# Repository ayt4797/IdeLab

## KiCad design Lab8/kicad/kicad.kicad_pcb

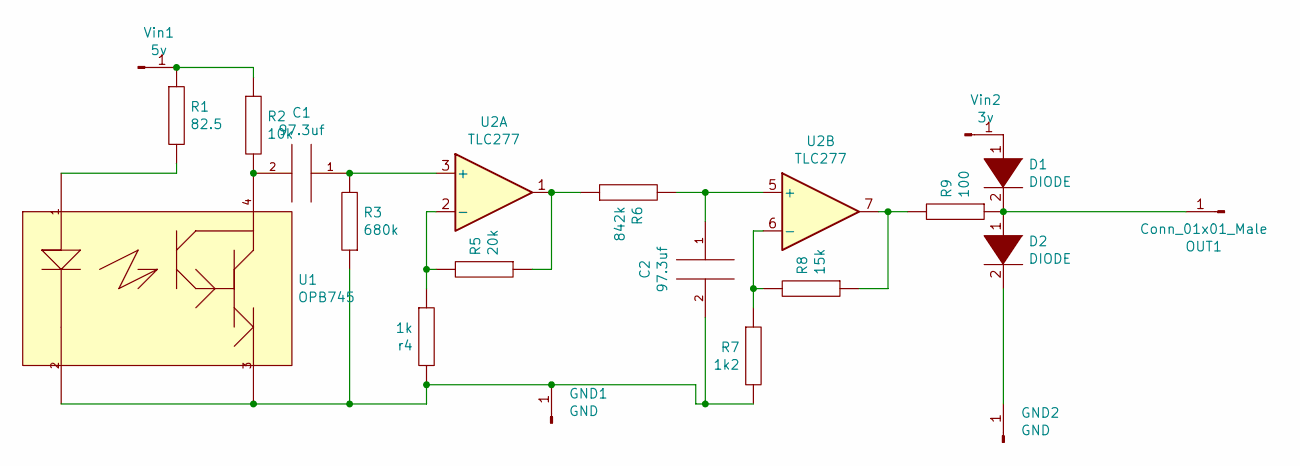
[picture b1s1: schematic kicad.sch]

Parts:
1k2: R7; R_Axial_DIN0204_L3.6mm_D1.6mm_P1.90mm_Vertical
C1, C2: 97.3uf; CP_Radial_D4.0mm_P1.50mm
D1, D2: DIODE; CP_Axial_L10.0mm_D4.5mm_P15.00mm_Horizontal
GND1, GND2: GND; PinHeader_1x01_P2.54mm_Horizontal
OUT1: Conn_01x01_Male; PinHeader_1x01_P2.54mm_Horizontal
R1: 82.5; R_Axial_DIN0204_L3.6mm_D1.6mm_P1.90mm_Vertical
R2: 10k; R_Axial_DIN0204_L3.6mm_D1.6mm_P1.90mm_Vertical
R3: 680k; R_Axial_DIN0204_L3.6mm_D1.6mm_P1.90mm_Vertical
R5: 20k; R_Axial_DIN0204_L3.6mm_D1.6mm_P1.90mm_Vertical
R6: 842k; R_Axial_DIN0204_L3.6mm_D1.6mm_P1.90mm_Vertical
R8: 15k; R_Axial_DIN0204_L3.6mm_D1.6mm_P1.90mm_Vertical
R9: 100; R_Axial_DIN0204_L3.6mm_D1.6mm_P1.90mm_Vertical
U1: OPB745; PinHeader_1x04_P2.54mm_Vertical; voltage 15V; mouser part number 828-OPB745; digikey description SENSR OPTO TRANS 3.81MM REFL PCB
U2: TLC277; DIP794W45P254L959H508Q8
Vin1: 5v; PinHeader_1x01_P2.54mm_Horizontal
Vin2: 3v; PinHeader_1x01_P2.54mm_Horizontal
r4: 1k; R_Axial_DIN0204_L3.6mm_D1.6mm_P1.90mm_Vertical

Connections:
unnamed: 1k2.1, R8.2, U2.6 (-)
unnamed: 1k2.2, C2.2, GND1.1, R3.1, U1.2 (Cathode), U1.3 (Emitter), r4.2
unnamed: C1.1, R3.2, U2.3 (+)
unnamed: C1.2, R2.2, U1.4 (Collector)
unnamed: C2.1, R6.2, U2.5 (+)
unnamed: D1.1 (K), Vin2.1
unnamed: D1.2 (A), D2.1 (K), OUT1.1, R9.1
unnamed: D2.2 (A), GND2.1
unnamed: R1.1, R2.1, Vin1.1
unnamed: R1.2, U1.1 (Anode)
unnamed: R5.1, R6.1, U2.1
unnamed: R5.2, U2.2 (-), r4.1
unnamed: R8.1, R9.2, U2.7

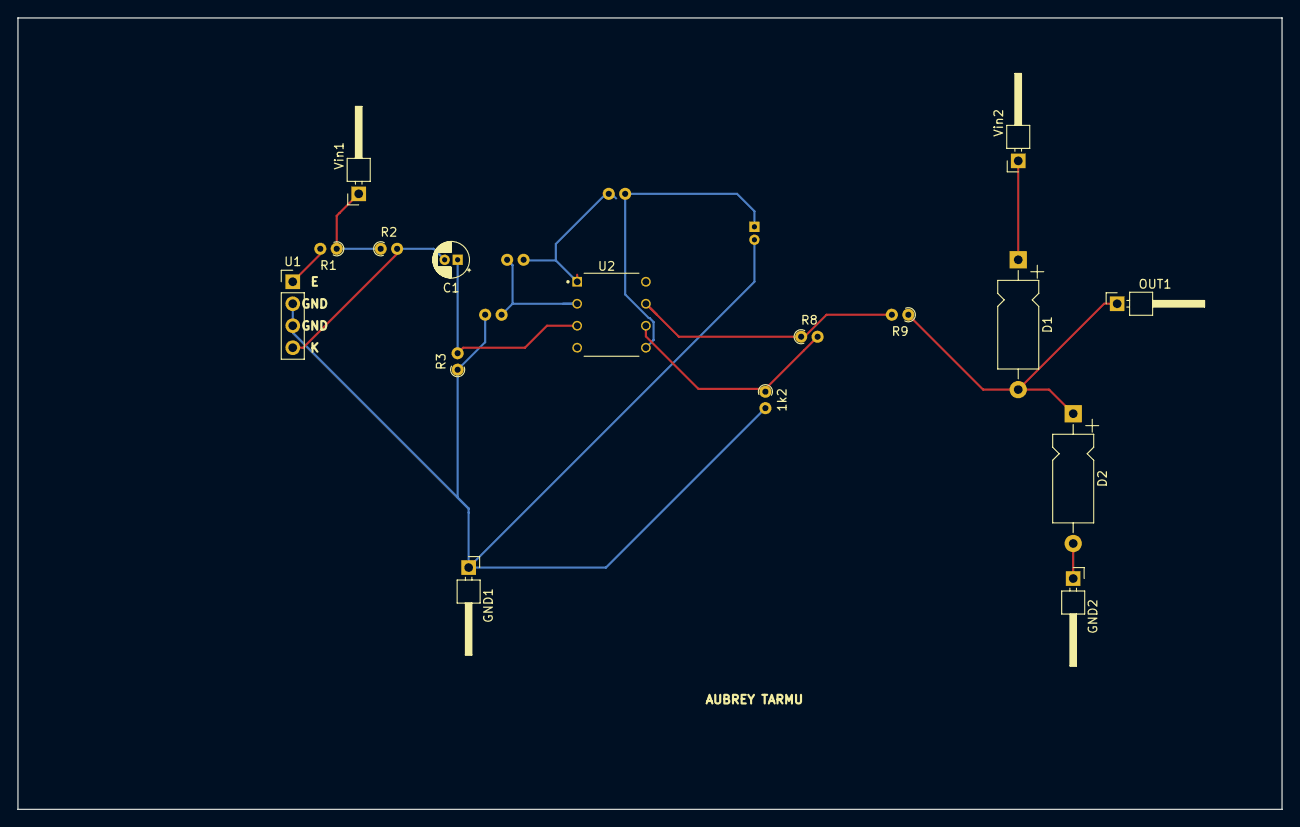
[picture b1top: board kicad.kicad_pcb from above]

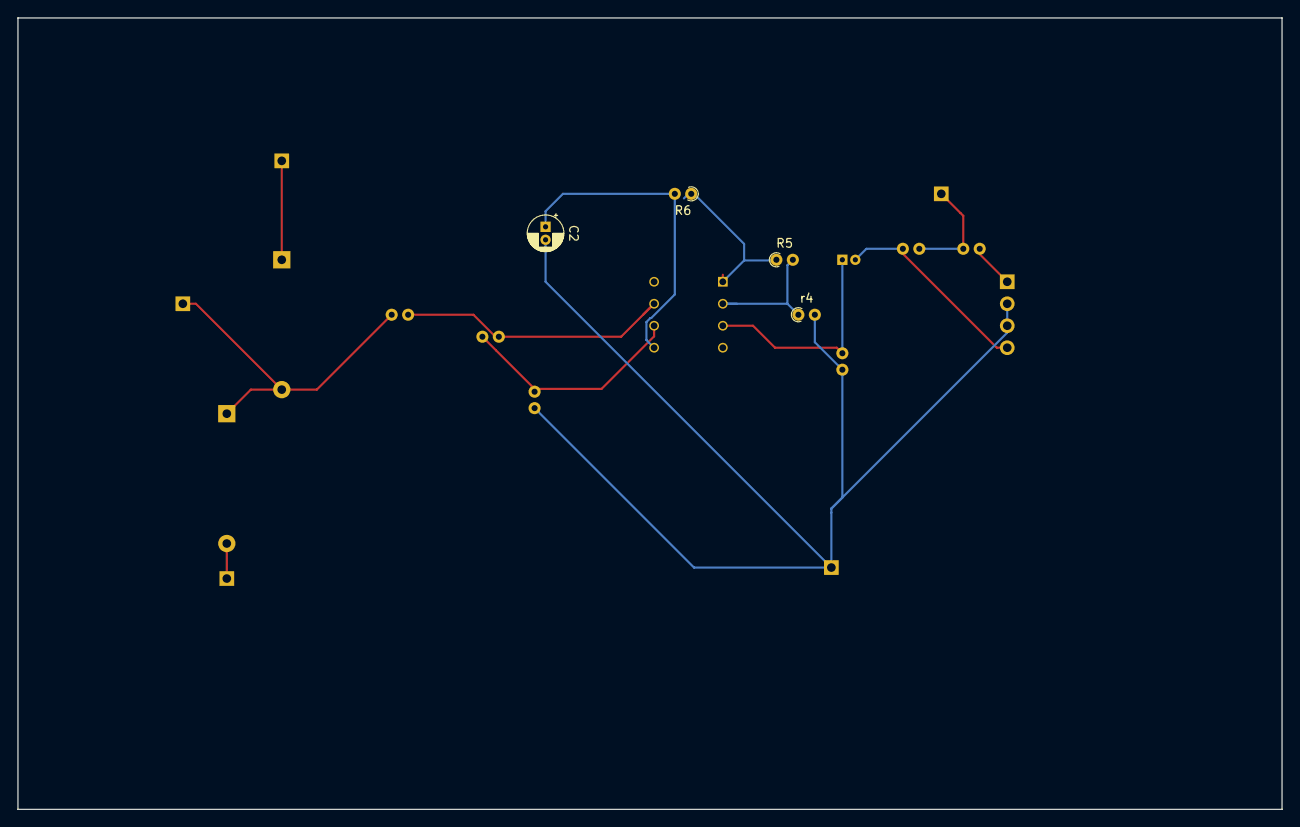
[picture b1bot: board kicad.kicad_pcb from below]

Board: 32 copper layers, 146.0 x 91.4 mm, 20 parts (4 on the bottom side), 13 nets.

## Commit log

2021-09-22 start
2021-09-24 work from friday lab
2021-10-01 part2a
2021-10-01 finished part2b
2021-10-01 systickTimer
2021-10-01 part3 start
2021-10-05 Dante's stuff
2021-10-08 real start
2021-10-09 lab 5 final
2021-10-14 10-14-21 working motor, but weird
2021-10-15 fcking git
2021-10-15 checkoff
2021-10-16 started part 3
2021-10-19 servo spinned
2021-10-19 minor changes
2021-10-21 check off part 3
2021-10-21 dante changes
2021-10-22 lab7 start
2021-10-22 100nf
2021-10-22 first order
2021-10-22 three order
2021-10-22 check off
2021-10-22 Added Lab6Stepper
2021-10-22 Added DCMotor
2021-10-22 Update DCMotor
2021-10-28 tst2
2021-10-28 reset file
2021-10-28 finnish sallen key
2021-10-28 butterworth
2021-10-28 fcking github
2021-10-29 finished
2021-10-29 prelab
2021-10-29 started adc
2021-10-29 labreport start lab7
2021-10-29 fixed the sallen key:
2021-11-04 fixing some small things w/ lab8 file
2021-11-04 basically haven't moved
2021-11-05 sign off 8
2021-11-06 project1 start
2021-11-06 added in lab4 stuff
2021-11-06 testing oled
2021-11-06 rewriting to print to both putty & bluetooth
2021-11-06 11/06/2021 Milestone 1 Almost Done
2021-11-06 bluetooth and oled setup
2021-11-06 moved the oled stuff to top
2021-11-06 balls
2021-11-06 added some stuff to my lab8
2021-11-06 nearly done w/8
2021-11-06 Near-final Milestone 1. Sign off required. Kp may need to be adjusted
2021-11-07 lab08
2021-11-07 nearly done w/ lab08
2021-11-08 removed that debug statement
2021-11-08 testing
2021-11-08 some kicad stuff
2021-11-08 near checkoff
2021-11-08 added osh screenshots
2021-11-08 added macros
2021-11-08 added some more directional control
2021-11-08 added some comments and a tolerance in case there's a camera mistake in the middle
2021-11-10 Corrections to inital commit
2021-11-10 Assembly changes
2021-11-10 Basic changes. Added debugging tools. Flipped Camera around. Found an issue with i being double defined from a for loop in the turn_left() function. Also renamed some functions
2021-11-10 Fucked with Integration time and camera focus. Camera scene is now 11791179
2021-11-11 Non ideal steering fix. based on main branch. Tolerance code is needed to minimize steering until absolutley need
2021-11-11 Additional changes to Kp. Changes to definition of control may be required
2021-11-11 theory
2021-11-11 Veriifed camera works
2021-11-11 Added debug changes. Changed integration time to match playingAround branch
2021-11-11 Adjusted integration time, adjusted thresehold. Overall pulled camera configuartion from playingAround
2021-11-11 New steering code
2021-11-11 Added fetch of current left and right to new steering
2021-11-11 Milestone 1 - recomplished
2021-11-11 derp
2021-11-11 Milestone 2 complete!
2021-11-11 Minor tweaks to speed and gain of proportional control
2021-11-11 removed old steering code
2021-11-12 found where the issue is, will ask seth for advice
2021-11-12 bluetooth works
2021-11-12 fixed some things
2021-11-12 fixed the clearance issue
2021-11-12 Refactoring of PID. Split up servo adjust for readability. Commeneted out BL adjustment since it needs to be cleaned up
2021-11-12 Minor changes.
2021-11-13 pcb done
2021-11-14 fixed some stuff
2021-11-15 Inital electric differential control
2021-11-15 Resolved error
2021-11-15 Minimum viable product. Includes straight away full bore speed. And moderatly refined P control
2021-11-15 working pid
2021-11-15 milestone 3
2021-11-15 Minor refactoring of PID solution
2021-11-17 Added new method to track going straight. Increased BAUD RATE to 115200. Added optimization logic
2021-11-18 Implemented PID. Minor oscillation still. Effective MVP
2021-11-18 MVP - Minor oscillations with PID on curvy track. She'll work tho. 70% of the time?
2021-11-18 MVP - Could use tolerance on going straight but otherwise PID control is 936$
2021-11-20 Changes made. Turning needs to be a lot more precise
2021-11-29 Reserve Commit
2021-12-01 Lowest Possible Speed
2021-12-01 added a left&right PID
2021-12-01 Preserving Recent Changes from today
2021-12-01 Debugging bad issues with turning right.
2021-12-01 fixed it poorly
2021-12-02 MVP 12/1/2021
2021-12-02 PID changes, turning speed changes required. New Braking system. Integration Hell. Will work with slower speeds
2021-12-02 cleaned some global variables
2021-12-03 mor minor things
2021-12-03 stuff
2021-12-03 more cleaning
2021-12-03 last clean
2021-12-03 kinda working
2021-12-03 super safe mode
2021-12-03 45sec
2021-12-03 removed old speed up stuff and fixed speed up
2021-12-03 increased gain
2021-12-03 some cleaning
2021-12-04 Inital commit from MVP_12_2_2021
2021-12-04 beginning of super safe mode
2021-12-04 went around the main track
2021-12-04 doesn't work
2021-12-04 went around again adding is off track threshold
2021-12-04 changed servo adjustments
